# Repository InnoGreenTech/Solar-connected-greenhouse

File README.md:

Solar connected greenhouse
==========================

Description:
------------

This is a autonome greenhouse with solar panels, a tank of water and a composter. It is also possible to control a garden.

This project is building around a Arduino Atmega 2560 and a ESP8266. The ESP8266 is optional, it allows to send data in a Json format. 

There are a lot of functionalities like spray, heating, orthicole lamp, fan, cat proof, … each is power by 24 Vdc provide by the solar pane. It can work with 48 Vdc or relay to work over voltage.

The system can measure humidity, temperature, moisture, CO2, level of water, … in several places. Each data can be send at a data center.

You can find drawing to build the same garden, greenhouse and lombricompost. I have provided the drawings.

There are also any stl files to make boxes for sensors and actuators. 

And the most important the drawings and PCB to make a main board with a
touch screen, a remote for the garden and a remote for the greenhouse.

Statut of project:
-----------------

Sensors of greenhouse:
color:green
1. Temperature
2. Humidity
3. Temperature of soil
4. Humidity of soil
5. Temperature of water
6. Level of water
7. CO2
8. Luminosity
color:black
Sensors of compost:
color:green
1. Temperature compost
2. Humidity compost
3. Voltage battery
4. Intensity battery
5. Intensity Load
color:black
Sensor of garden:
color:green
1. Temperature out
2. Humidity out
3. Temperature soil
4. Humidity soil
color:black
Actuators of greenhouse:
color:green
1. Pump of cooling system
2. Fans of cooling system
3. Fan of VMC
4. Servo motor of VMC clap
5. Horticol lamp
color:black
Actuators of Compost and garden:
color:green
1. Heating compost
2. Main pump spray
3. EV spray Green house
4. EV spray garden
5. EV spray lombric

color:black

[*You can also follow this project here*](http://innogreentech.fr) 

[*A complete description to make electronic boards*](http://innogreentech.fr/en/green-side/green-food/20-serre-connectee/53-electronic-board-for-the-solar-greenhouse)

[*A dash board to follow my personal project*](http://innogreentech.fr/fr/cote-green/nourriture/serre-et-potager-connectes/45-serre-connectee-en-direct)

**Contributing**

Fork it
Create your feature branch (git checkout -b my-new-feature)
Commit your changes (git commit -am 'Add some feature')
Push to the branch (git push origin my-new-feature)
Create new Pull Request

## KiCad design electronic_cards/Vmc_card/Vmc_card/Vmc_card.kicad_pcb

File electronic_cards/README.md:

Electronics cards
==================

Here you can found the drawings and the pcb to make electronics boards.

- Main board
- Remote greenhouse board
- Remoten garden board
- Greenhouse sensors board (for a DHT22, a Photo resistor and a CO2 sensor MH-Z19B)
- Vmc board to connect fan and servo flap

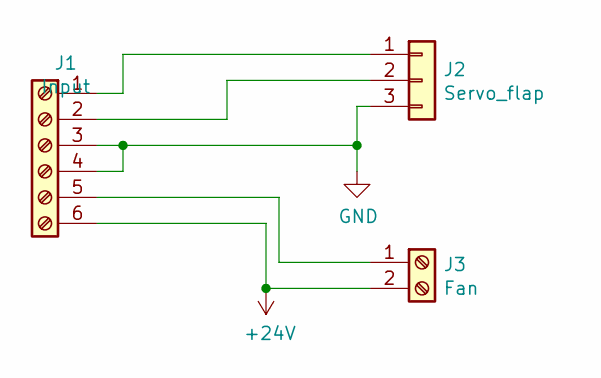
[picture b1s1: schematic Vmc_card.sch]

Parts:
J1: Input; TerminalBlock_4Ucon_1x06_P3.50mm_Horizontal
J2: Servo_flap; PinHeader_1x03_P2.54mm_Vertical
J3: Fan; TerminalBlock_4Ucon_1x02_P3.50mm_Horizontal

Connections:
+24V: J1.6, J3.2
GND: J1.3, J1.4, J2.3
unnamed: J1.1, J2.1
unnamed: J1.2, J2.2
unnamed: J1.5, J3.1

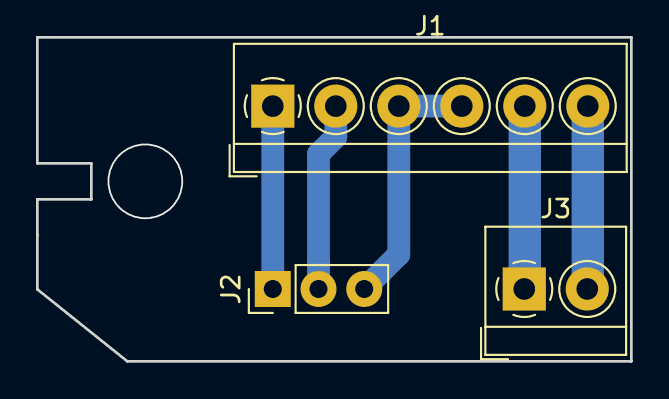
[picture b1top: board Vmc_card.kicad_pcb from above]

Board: 2 copper layers, 33.0 x 18.0 mm, 3 parts (0 on the bottom side), 5 nets.

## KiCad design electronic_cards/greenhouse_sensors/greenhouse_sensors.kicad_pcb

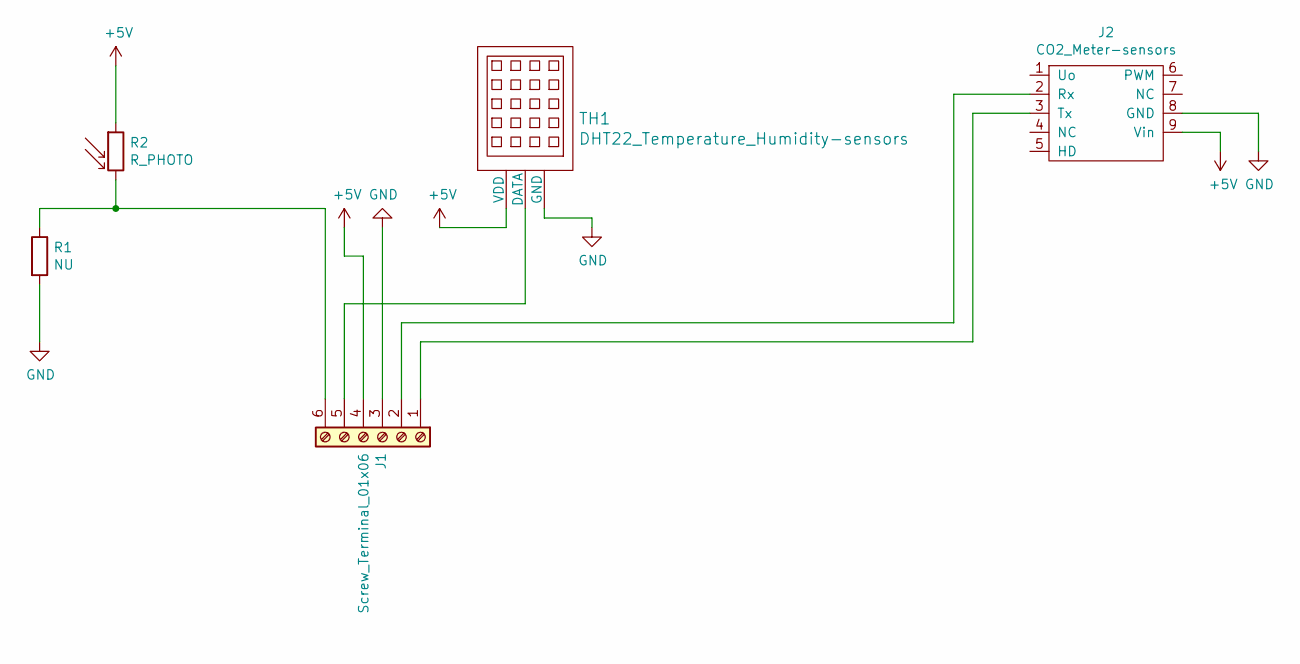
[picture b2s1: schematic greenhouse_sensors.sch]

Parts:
J1: Screw_Terminal_01x06; TerminalBlock_MetzConnect_Type059_RT06306HBWC_1x06_P3.50mm_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
J2: CO2_Meter-sensors; MHZ19B
R1: NU; R_Axial_DIN0207_L6.3mm_D2.5mm_P7.62mm_Horizontal
R2: R_PHOTO; R_Axial_DIN0204_L3.6mm_D1.6mm_P5.08mm_Vertical
TH1: DHT22_Temperature_Humidity-sensors; DHT22_Temperature_Humidity

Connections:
+5V: J1.4, J2.9 (Vin), R2.1, TH1.1 (VDD)
GND: J1.3, J2.8 (GND), R1.2, TH1.3 (GND)
unnamed: J1.1, J2.3 (Tx)
unnamed: J1.2, J2.2 (Rx)
unnamed: J1.5, TH1.2 (DATA)
unnamed: J1.6, R1.1, R2.2

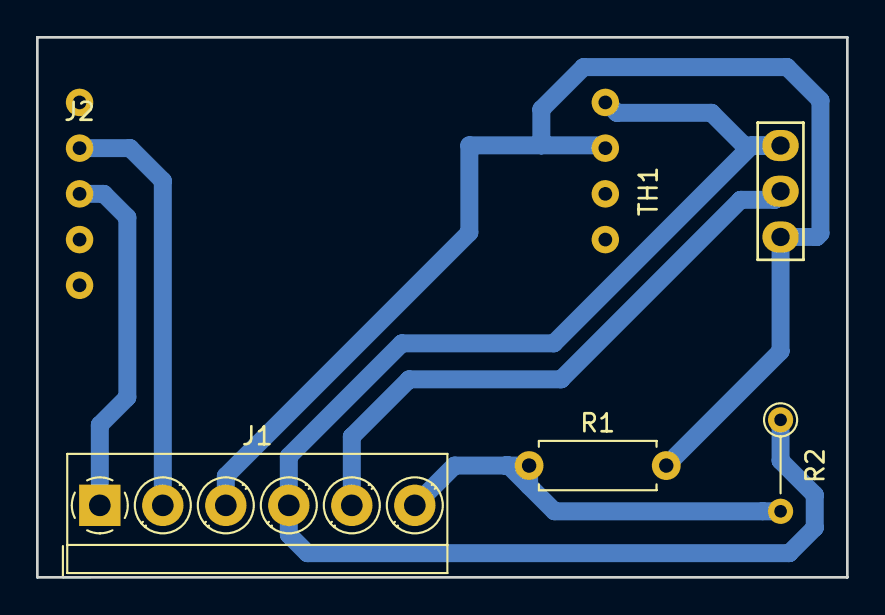
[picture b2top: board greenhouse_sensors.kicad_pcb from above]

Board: 2 copper layers, 45.0 x 30.0 mm, 5 parts (0 on the bottom side), 6 nets.

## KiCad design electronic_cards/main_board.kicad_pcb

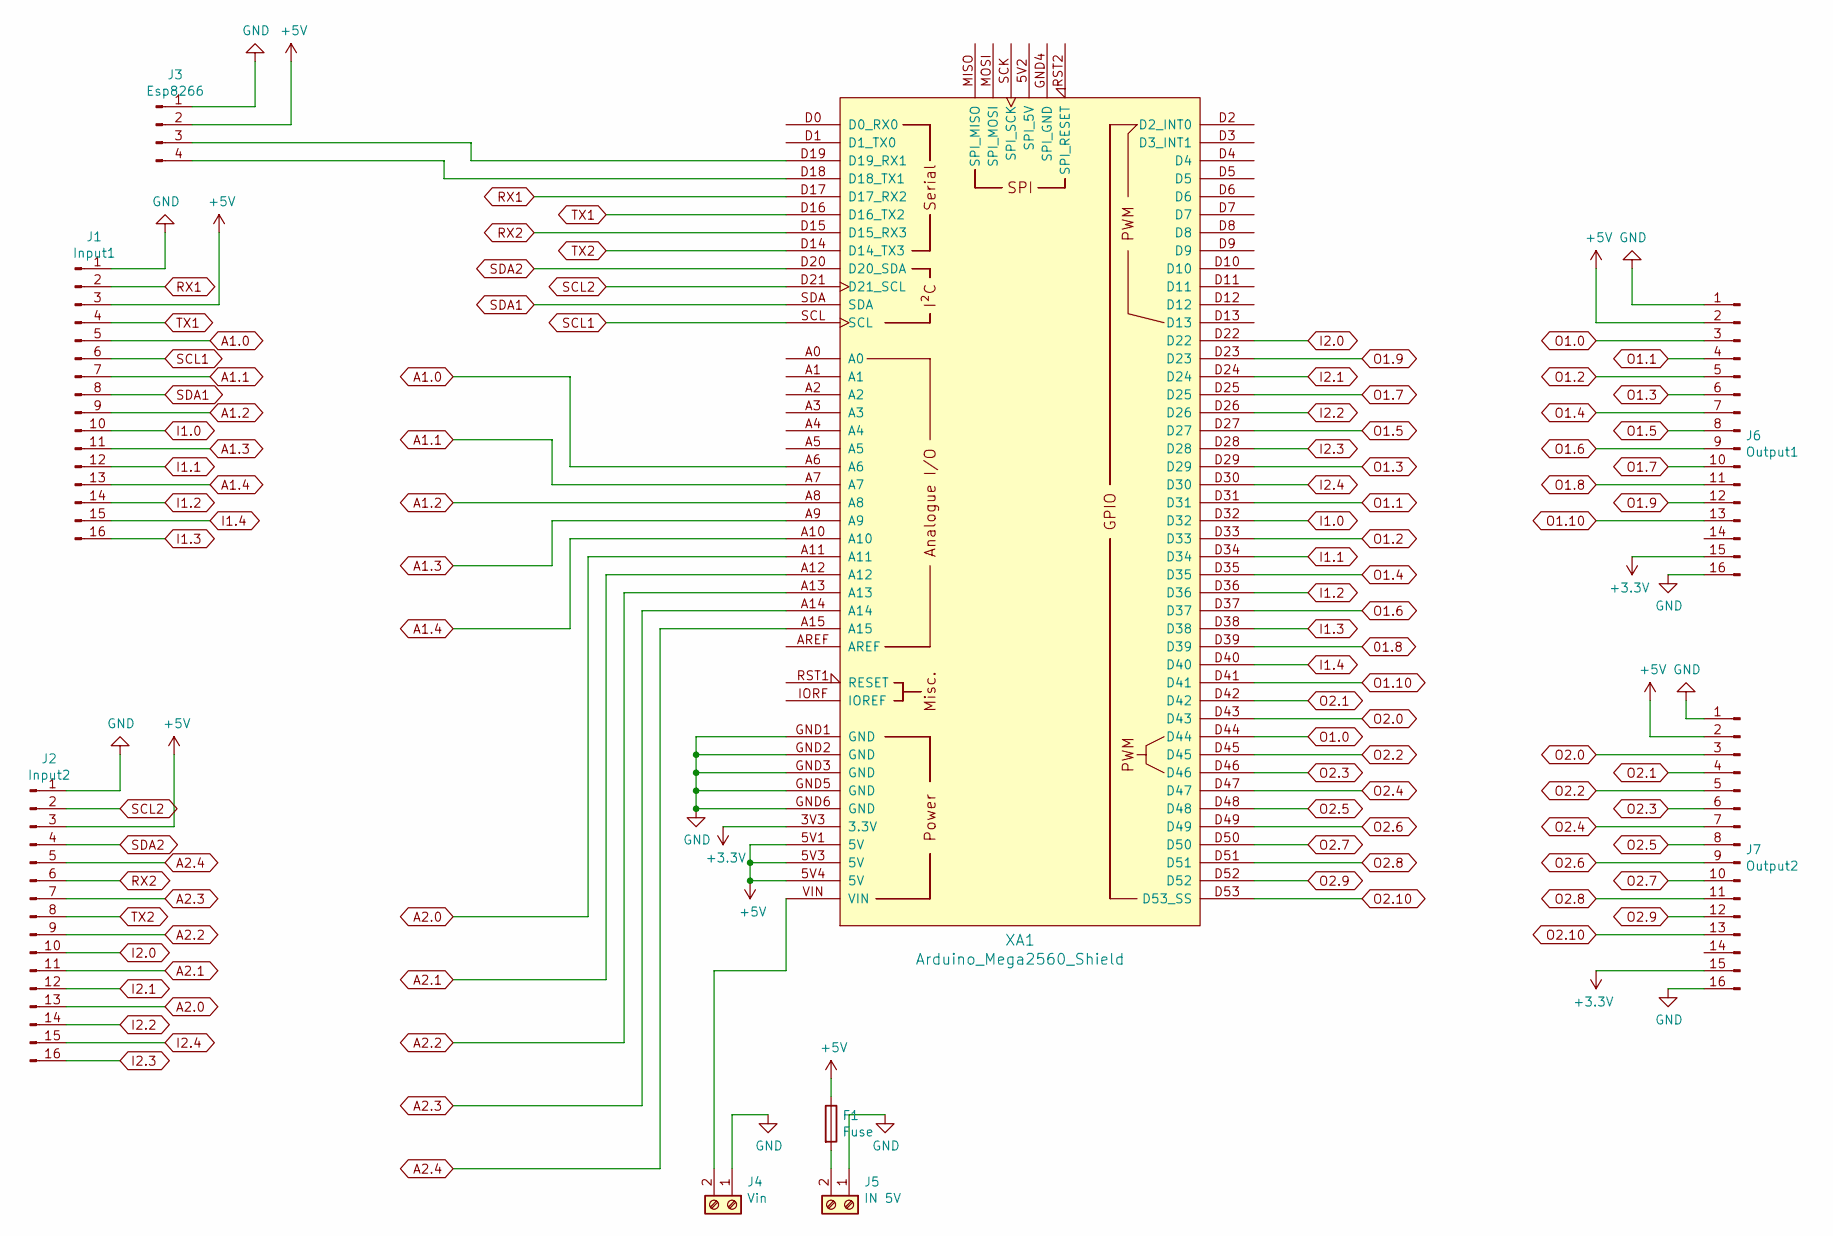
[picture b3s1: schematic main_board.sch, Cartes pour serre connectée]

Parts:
F1: Fuse; R_Axial_DIN0207_L6.3mm_D2.5mm_P7.62mm_Horizontal
J1: Input1; IDC-Header_2x08_P2.54mm_Vertical
J2: Input2; IDC-Header_2x08_P2.54mm_Vertical
J3: Esp8266; PinHeader_1x04_P2.54mm_Vertical
J4: Vin; SolderWirePad_1x02_P5.08mm_Drill1.5mm
J5: IN 5V; SolderWirePad_1x02_P5.08mm_Drill1.5mm
J6: Output1; IDC-Header_2x08_P2.54mm_Vertical
J7: Output2; IDC-Header_2x08_P2.54mm_Vertical
XA1: Arduino_Mega2560_Shield

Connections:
01.8: XA1.D39
+3V3: J6.15, J7.15, XA1.3V3 (3.3V)
+5V: F1.1, J1.3, J2.3, J3.2, J6.2, J7.2, XA1.5V1 (5V), XA1.5V3 (5V), XA1.5V4 (5V)
A1.0: J1.5, XA1.A6
A1.1: J1.7, XA1.A7
A1.2: J1.9, XA1.A8
A1.3: J1.11, XA1.A9
A1.4: J1.13, XA1.A10
A2.0: J2.13, XA1.A11
A2.1: J2.11, XA1.A12
A2.2: J2.9, XA1.A13
A2.3: J2.7, XA1.A14
A2.4: J2.5, XA1.A15
GND: J1.1, J2.1, J3.1, J4.1, J5.1, J6.1, J6.16, J7.1, J7.16, XA1.GND1 (GND), XA1.GND2 (GND), XA1.GND3 (GND), XA1.GND5 (GND), XA1.GND6 (GND)
I1.0: J1.10, XA1.D32
I1.1: J1.12, XA1.D34
I1.2: J1.14, XA1.D36
I1.3: J1.16, XA1.D38
I1.4: J1.15, XA1.D40
I2.0: J2.10, XA1.D22
I2.1: J2.12, XA1.D24
I2.2: J2.14, XA1.D26
I2.3: J2.16, XA1.D28
I2.4: J2.15, XA1.D30
unnamed: F1.2, J5.2
unnamed: J3.3, XA1.D19 (D19_RX1)
unnamed: J3.4, XA1.D18 (D18_TX1)
unnamed: J4.2, XA1.VIN
O1.0: J6.3, XA1.D44
O1.1: J6.4, XA1.D31
O1.2: J6.5, XA1.D33
O1.3: J6.6, XA1.D29
O1.4: J6.7, XA1.D35
O1.5: J6.8, XA1.D27
O1.6: J6.9, XA1.D37
O1.7: J6.10, XA1.D25
O1.8: J6.11
O1.9: J6.12, XA1.D23
O1.10: J6.13, XA1.D41
O2.0: J7.3, XA1.D43
O2.1: J7.4, XA1.D42
O2.2: J7.5, XA1.D45
O2.3: J7.6, XA1.D46
O2.4: J7.7, XA1.D47
O2.5: J7.8, XA1.D48
O2.6: J7.9, XA1.D49
O2.7: J7.10, XA1.D50
O2.8: J7.11, XA1.D51
O2.9: J7.12, XA1.D52
O2.10: J7.13, XA1.D53 (D53_SS)
RX1: J1.2, XA1.D17 (D17_RX2)
RX2: J2.6, XA1.D15 (D15_RX3)
SCL1: J1.6, XA1.SCL
SCL2: J2.2, XA1.D21 (D21_SCL)
SDA1: J1.8, XA1.SDA
SDA2: J2.4, XA1.D20 (D20_SDA)
TX1: J1.4, XA1.D16 (D16_TX2)
TX2: J2.8, XA1.D14 (D14_TX3)

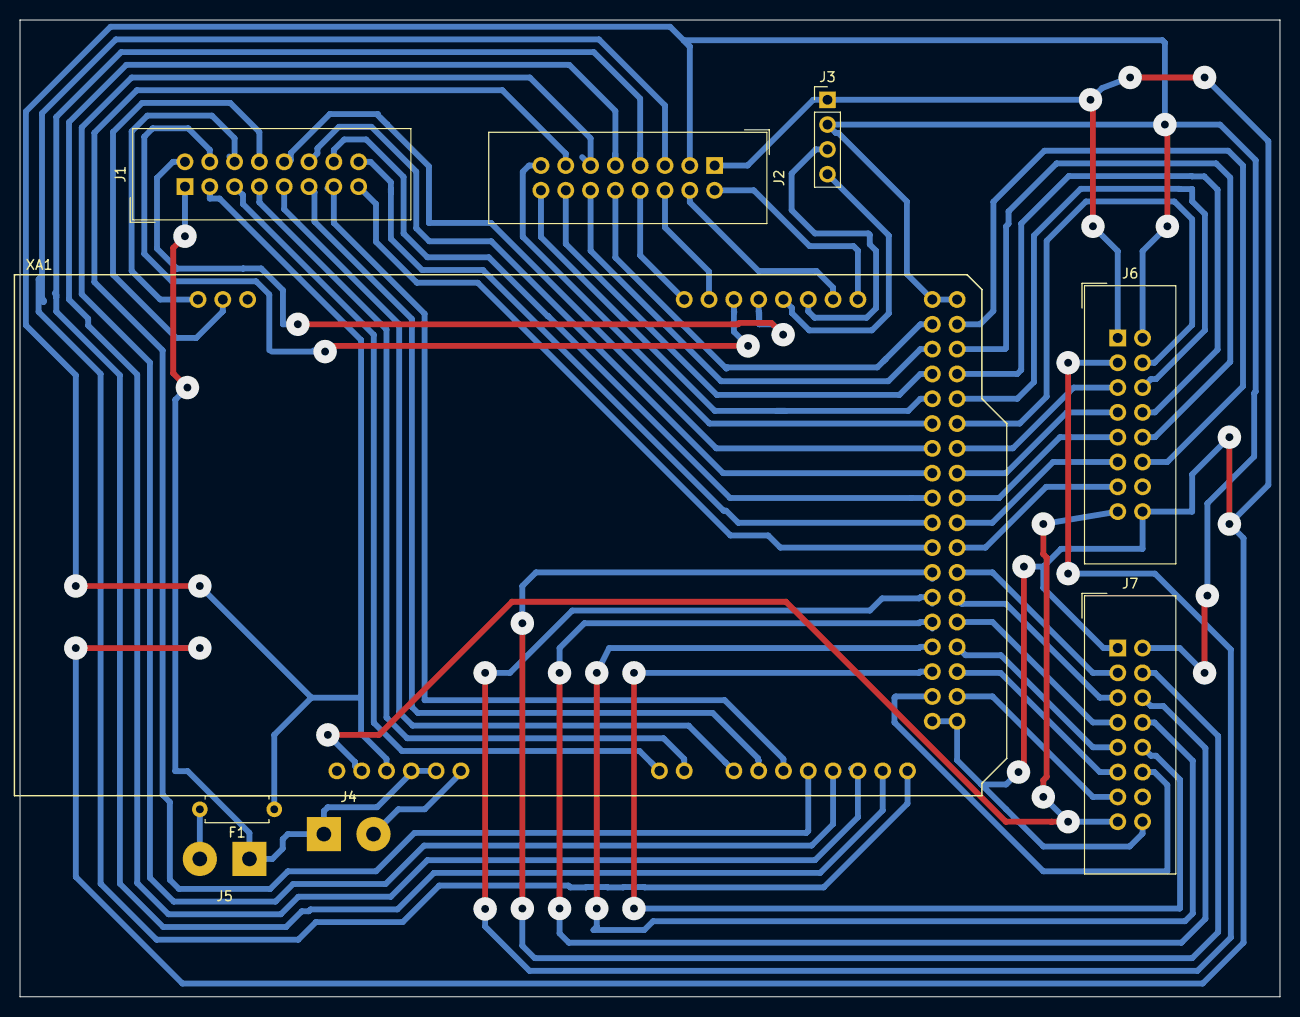
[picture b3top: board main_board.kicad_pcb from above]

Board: 2 copper layers, 129.0 x 100.0 mm, 9 parts (0 on the bottom side), 56 nets.

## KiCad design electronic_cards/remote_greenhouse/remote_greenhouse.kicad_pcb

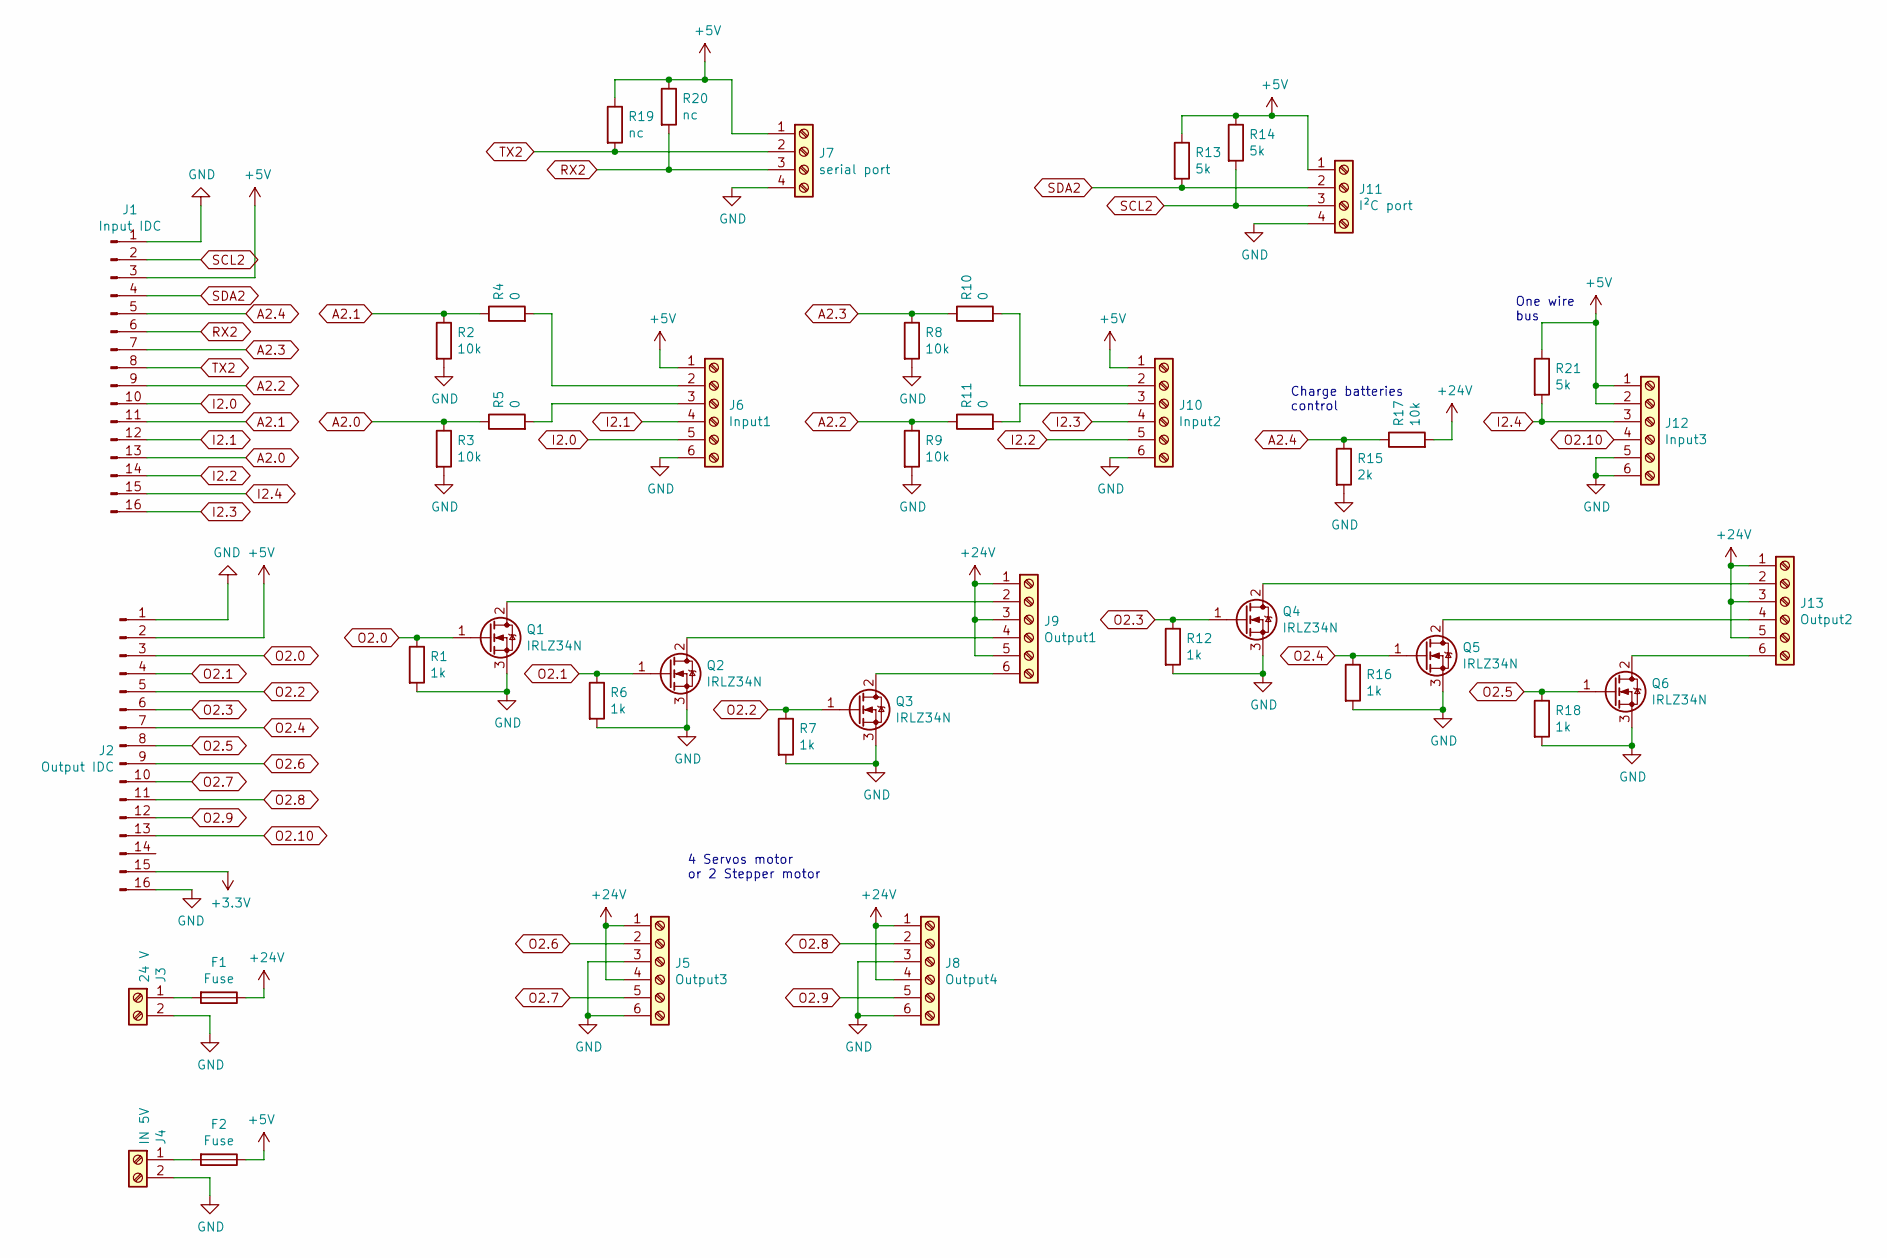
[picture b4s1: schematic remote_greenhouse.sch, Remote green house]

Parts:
F1, F2: Fuse; Fuse_Littelfuse_395Series
J1: Input IDC; IDC-Header_2x08_P2.54mm_Vertical
J2: Output IDC; IDC-Header_2x08_P2.54mm_Vertical
J3: 24 V; TerminalBlock_MetzConnect_Type101_RT01602HBWC_1x02_P5.08mm_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
J4: IN 5V; TerminalBlock_MetzConnect_Type086_RT03402HBLC_1x02_P3.81mm_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
J5: Output3; TerminalBlock_MetzConnect_Type101_RT01606HBWC_1x06_P5.08mm_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
J6: Input1; TerminalBlock_MetzConnect_Type086_RT03406HBLC_1x06_P3.81mm_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
J7: serial port; TerminalBlock_MetzConnect_Type086_RT03404HBLC_1x04_P3.81mm_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
J8: Output4; TerminalBlock_MetzConnect_Type101_RT01606HBWC_1x06_P5.08mm_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
J9: Output1; TerminalBlock_MetzConnect_Type101_RT01606HBWC_1x06_P5.08mm_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
J10: Input2; TerminalBlock_MetzConnect_Type086_RT03406HBLC_1x06_P3.81mm_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
J11: I²C port; TerminalBlock_MetzConnect_Type086_RT03404HBLC_1x04_P3.81mm_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
J12: Input3; TerminalBlock_MetzConnect_Type086_RT03406HBLC_1x06_P3.81mm_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
J13: Output2; TerminalBlock_MetzConnect_Type101_RT01606HBWC_1x06_P5.08mm_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
Q1, Q2, Q3, Q4, Q5, Q6: IRLZ34N; TO-220-3_Vertical
R1, R6, R7, R12, R16, R18: 1k; R_Axial_DIN0207_L6.3mm_D2.5mm_P7.62mm_Horizontal
R2, R3, R8, R9, R17: 10k; R_Axial_DIN0207_L6.3mm_D2.5mm_P7.62mm_Horizontal
R4, R5, R10, R11: 0; R_Axial_DIN0207_L6.3mm_D2.5mm_P7.62mm_Horizontal
R13, R14, R21: 5k; R_Axial_DIN0207_L6.3mm_D2.5mm_P7.62mm_Horizontal
R15: 2k; R_Axial_DIN0207_L6.3mm_D2.5mm_P7.62mm_Horizontal
R19, R20: nc; R_Axial_DIN0207_L6.3mm_D2.5mm_P7.62mm_Horizontal

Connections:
+3V3: J2.15
+5V: F2.1, J1.3, J2.2, J6.1, J7.1, J10.1, J11.1, J12.1, J12.2, R13.1, R14.1, R19.1, R20.1, R21.1
+24V: F1.1, J5.1, J5.4, J8.1, J8.4, J9.1, J9.3, J9.5, J13.1, J13.3, J13.5, R17.2
A2.0: J1.13, R3.1, R5.1
A2.1: J1.11, R2.1, R4.1
A2.2: J1.9, R9.1, R11.1
A2.3: J1.7, R8.1, R10.1
A2.4: J1.5, R15.1, R17.1
GND: J1.1, J2.1, J2.16, J3.2, J4.2, J5.3, J5.6, J6.6, J7.4, J8.3, J8.6, J10.6, J11.4, J12.5, J12.6, Q1.3 (S), Q2.3 (S), Q3.3 (S), Q4.3 (S), Q5.3 (S), Q6.3 (S), R1.2, R2.2, R3.2, R6.2, R7.2, R8.2, R9.2, R12.2, R15.2, R16.2, R18.2
I2.0: J1.10, J6.5
I2.1: J1.12, J6.4
I2.2: J1.14, J10.5
I2.3: J1.16, J10.4
I2.4: J1.15, J12.3, R21.2
unnamed: F1.2, J3.1
unnamed: F2.2, J4.1
unnamed: J6.2, R4.2
unnamed: J6.3, R5.2
unnamed: J9.2, Q1.2 (D)
unnamed: J9.4, Q2.2 (D)
unnamed: J9.6, Q3.2 (D)
unnamed: J10.2, R10.2
unnamed: J10.3, R11.2
unnamed: J13.2, Q4.2 (D)
unnamed: J13.4, Q5.2 (D)
unnamed: J13.6, Q6.2 (D)
O2.0: J2.3, Q1.1 (G), R1.1
O2.1: J2.4, Q2.1 (G), R6.1
O2.2: J2.5, Q3.1 (G), R7.1
O2.3: J2.6, Q4.1 (G), R12.1
O2.4: J2.7, Q5.1 (G), R16.1
O2.5: J2.8, Q6.1 (G), R18.1
O2.6: J2.9, J5.2
O2.7: J2.10, J5.5
O2.8: J2.11, J8.2
O2.9: J2.12, J8.5
O2.10: J2.13, J12.4
RX2: J1.6, J7.3, R20.2
SCL2: J1.2, J11.3, R14.2
SDA2: J1.4, J11.2, R13.2
TX2: J1.8, J7.2, R19.2

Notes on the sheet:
Charge batteries control
4 Servos motor or 2 Stepper motor
One wire bus

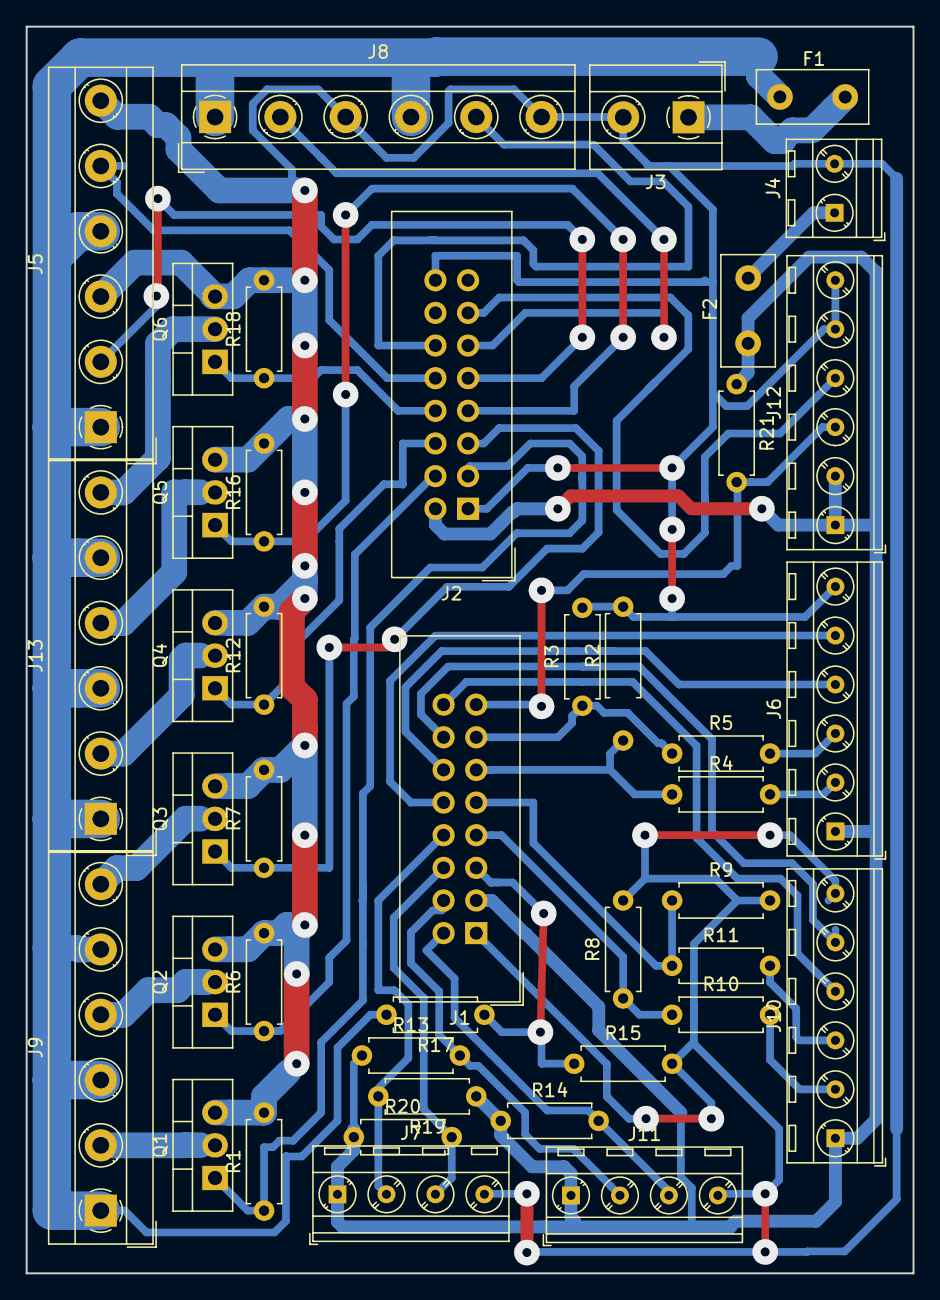
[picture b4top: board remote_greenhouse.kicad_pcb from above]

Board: 2 copper layers, 69.0 x 97.0 mm, 42 parts (0 on the bottom side), 40 nets.

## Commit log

2020-01-01 Informations suplémentaires dans le fichier Readme
2020-01-01 informations suplémentaires sur readme innogreentech.fr
2020-01-01 Ajout des fichiers de la photo d'acceuil
2020-01-02 ajout du fichier .gitignore
2020-01-02 Non nécessaire au projet
2020-01-02 non nécessaire a projet
2020-01-02 Ajout du fichier de licence
2020-01-02 New readme content
2020-01-04 Create file of the first version of arduino software
2020-01-05 The first version of the wifi connection (not work in the state)
2020-01-10 Update with a version ready to test
2020-01-10 test color readme file
2020-01-11 output control update
2020-01-12 Correctrion of PCB, RX and TX of ESP were inverted
2020-01-14 Add how to contribute at this poject
2020-01-16 Correction of many bugs on the communication between arduino and esp
2020-01-16 improve web page information
2020-01-19 Improve communication between Esp and arduino
2020-01-25 befor implement vmc controler
2020-02-02 Add Vmc control and remove any bugs
2020-02-03 modify Read file
2020-02-08 change out sensor by BME280, add setting parameters
2020-02-09 improve measure of intensity and voltage
2020-02-20 change level water sensor
2020-02-20 update readme file
2020-02-25 Add weather forecasts and improve moist sensors. I add 3 parameters , 2 for moisture sensors, and 1 for altitude parameter
2020-02-25 Add file to control mode on greenhouse
2020-02-25 update information
2020-02-26 Add weather forecasts on the main screen
2020-03-08 update ESP software to protec wrong sent values
2020-03-08 improve sent data
2020-03-14 New VMC control
2020-03-22 add watch dog control and average humidity and temperature day
2020-03-29 Add hydroponie fonctionnality and change probe for compost, use DS18B20 in place of BME 280
2020-04-26 add automatic spray, and spray for a external gardening
2020-04-29 Automatic spray improve
2020-05-04 little correctif
2020-05-11 add manual spray form in web page, add spray out_garden control
2020-05-21 update spray control
2020-05-24 change methode of heating composter, use cooling sytem
2020-06-08 New level water sensor, pressure sensor
2020-06-14 debug new method to measure level of water
2020-07-11 update spray
2020-07-12 realease a test on the board
2020-07-14 Correction level water with temperature greenhouse
2020-07-16 update average day humidity
2020-08-15 Use water proof sonar for the level of water
2020-09-16 add two fonctionnalities, heat water with solar energy too much, and a cooling water when the weather is too hot
2020-09-17 Debug new fonctionnalities
2021-04-23 desable PID , and active intensity to adjust recover power
